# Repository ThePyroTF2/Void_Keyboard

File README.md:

Void Keyboard
====
A while ago I saw [this video](https://www.youtube.com/watch?v=H_Ym9528awM) looking at [Riskable](https://github.com/Riskable)'s [Void Switches](https://github.com/Riskable/void_switch) and it immediately caught my fancy.
They were new, cool, and most importantly, you could make em yourself with relative ease.

Now, I'm making an entire keyboard from scratch.

huh.

PCB
----
Because of the nature of the switches, a keyboard using them would be analog using hall effect sensors. Thing is, there isn't any analog hall effect PCBs on the market right now, mainly because analog keyboards as a whole are fairly new, so anybody wanting to make a keyboard using Void Switches has to make their own PCB from scratch.
And, with help from Riskable, I'm doing that.

I've never worked with PCB stuff before, but I'm learning pretty quickly and while I feel a bit out of my league progress is going rather smoothly. The PCB takes a lot of time not because it's complex, but because it's got **112** keys.

I'm lucky enough to be going to an engineering magnet program at my high school so I _should_ have access to soldering tools and the like, although I'm not 100% certain. If not, I'll find a way.

Switches
----
Don't exist right now! I do know, however, that I can use my school's 3d printers to make em.

Case
----
No clue how the case is gonna go. Could I machine it at school? should I just be happy with printing it out? does i even frickin matter? Who knows?! All I presently care about is getting the circuitry done.

Firmware
----
The most important part to making a keyboard is the firmware. Without it, keyboard no make letters on screen. Thing is, Riskable is still working on it! I hope to help him out and I'll update with more information as time goes on, but as it stands I've got nothing here.

Overall stuffs
====
This is really cool for me. I can't wait to get it done. It's hella fun to learn this stuff and make something really tangible and working and I would really recommend you do it too.

Novel things I wanna try to do with this
----
* Variable volume changes

You may notice that I have volume controls using hall effect sensors as well. In all honesty, it mainly just makes it easier to work with, but I want to try something cool with increasing and decreasing the volume.
I want to make it so that the amount that the volume increases or decreases depends on how far you push the volume button down. The 100% down amount can change using the config, but I think it'd be cool

* Turbo mode

I'm thinking I make a fun button (the most obvious key that could be replaced for fun would be the options key) toggle a kind of turbo mode, where the further down you push a key the faster it goes. I'm not sure just how useful that would be, but it's an idea.

I'm going to keep brainstorming what kind of things could be done with analog inputs.

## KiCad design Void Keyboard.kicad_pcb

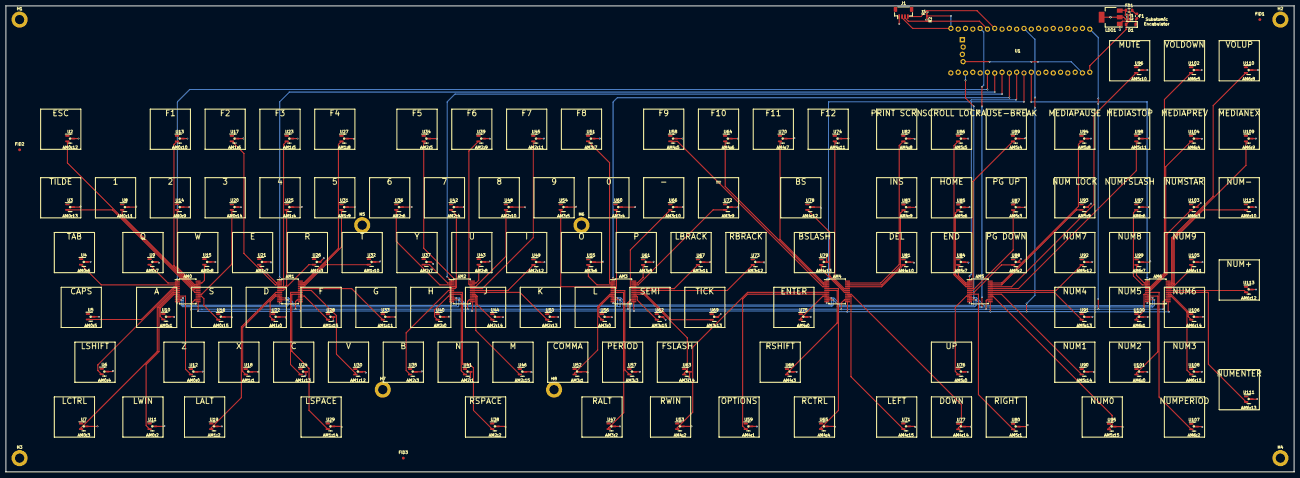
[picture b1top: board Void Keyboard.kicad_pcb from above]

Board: 2 copper layers, 447.7 x 161.9 mm, 252 parts (0 on the bottom side), 130 nets.

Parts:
AM0, AM1, AM2, AM3, AM4, AM5, AM6: CD74HC4067SM; SSOP-24_5.3x8.2mm_P0.65mm
AM0:0: Z; VoidSwitch_1u_SMD
AM0:1: VoidSwitch1U; VoidSwitch_1u_SMD
AM0:2: LWIN; VoidSwitch_1u_SMD
AM0:3: LCTRL; VoidSwitch_1.5u_SMD
AM0:4: LSHIFT; VoidSwitch_2.25u_SMD
AM0:5: CAPS; VoidSwitch_1.75u_SMD
AM0:6: TAB; VoidSwitch_1.5u_SMD
AM0:7: Q; VoidSwitch_1u_SMD
AM0:8: W; VoidSwitch_1u_SMD
AM0:9: 2; VoidSwitch_1u_SMD
AM0:10: F1; VoidSwitch_1u_SMD
AM0:11: 1; VoidSwitch_1u_SMD
AM0:12: ESC; VoidSwitch_1u_SMD
AM0:13: TILDE; VoidSwitch_1u_SMD
AM0:14: 3; VoidSwitch_1u_SMD
AM0:15: S; VoidSwitch_1u_SMD
AM1:0: D; VoidSwitch_1u_SMD
AM1:1: X; VoidSwitch_1u_SMD
AM1:2: LALT; VoidSwitch_1.25u_SMD
AM1:3: R; VoidSwitch_1u_SMD
AM1:4: 4; VoidSwitch_1u_SMD
AM1:5: F3; VoidSwitch_1u_SMD
AM1:6: F2; VoidSwitch_1u_SMD
AM1:7: E; VoidSwitch_1u_SMD
AM1:8: F4; VoidSwitch_1u_SMD
AM1:9: 5; VoidSwitch_1u_SMD
AM1:10: T; VoidSwitch_1u_SMD
AM1:11: G; VoidSwitch_1u_SMD
AM1:12: V; VoidSwitch_1u_SMD
AM1:13: C; VoidSwitch_1u_SMD
AM1:14: LSPACE; VoidSwitch_3u_SMD
AM1:15: F; VoidSwitch_1u_SMD
AM2:0: H; VoidSwitch_1u_SMD
AM2:1: N; VoidSwitch_1u_SMD
AM2:2: RSPACE; VoidSwitch_3u_SMD
AM2:3: B; VoidSwitch_1u_SMD
AM2:4: 7; VoidSwitch_1u_SMD
AM2:5: F5; VoidSwitch_1u_SMD
AM2:6: 6; VoidSwitch_1u_SMD
AM2:7: Y; VoidSwitch_1u_SMD
AM2:8: U; VoidSwitch_1u_SMD
AM2:9: F6; VoidSwitch_1u_SMD
AM2:10: 8; VoidSwitch_1u_SMD
AM2:11: F7; VoidSwitch_1u_SMD
AM2:12: I; VoidSwitch_1u_SMD
AM2:13: K; VoidSwitch_1u_SMD
AM2:14: J; VoidSwitch_1u_SMD
AM2:15: M; VoidSwitch_1u_SMD
AM3:0: L; VoidSwitch_1u_SMD
AM3:1: COMMA; VoidSwitch_1u_SMD
AM3:2: RALT; VoidSwitch_1.25u_SMD
AM3:3: PERIOD; VoidSwitch_1u_SMD
AM3:4: 0; VoidSwitch_1u_SMD
AM3:5: 9; VoidSwitch_1u_SMD
AM3:6: O; VoidSwitch_1u_SMD
AM3:7: F8; VoidSwitch_1u_SMD
AM3:8: P; VoidSwitch_1u_SMD
AM3:9: =; VoidSwitch_1u_SMD
AM3:10: -; VoidSwitch_1u_SMD
AM3:11: LBRACK; VoidSwitch_1u_SMD
AM3:12: RBRACK; VoidSwitch_1u_SMD
AM3:13: TICK; VoidSwitch_1u_SMD
AM3:14: FSLASH; VoidSwitch_1u_SMD
AM3:15: SEMI; VoidSwitch_1u_SMD
AM4:0: ENTER; VoidSwitch_2.25u_SMD
AM4:1: OPTIONS; VoidSwitch_1.25u_SMD
AM4:2: RWIN; VoidSwitch_1.25u_SMD
AM4:3: RSHIFT; VoidSwitch_2.75u_SMD
AM4:4: RCTRL; VoidSwitch_1.5u_SMD
AM4:5: F9; VoidSwitch_1u_SMD
AM4:6: F10; VoidSwitch_1u_SMD
AM4:7: F11; VoidSwitch_1u_SMD
AM4:8: PRINT SCRN; VoidSwitch_1u_SMD
AM4:9: INS; VoidSwitch_1u_SMD
AM4:10: DEL; VoidSwitch_1u_SMD
AM4:11: F12; VoidSwitch_1u_SMD
AM4:12: BS; VoidSwitch_2u_SMD
AM4:13: BSLASH; VoidSwitch_1.5u_SMD
AM4:14: DOWN; VoidSwitch_1u_SMD
AM4:15: LEFT; VoidSwitch_1u_SMD
AM5:0: UP; VoidSwitch_1u_SMD
AM5:1: RIGHT; VoidSwitch_1u_SMD
AM5:2: PG DOWN; VoidSwitch_1u_SMD
AM5:3: PG UP; VoidSwitch_1u_SMD
AM5:4: PAUSE-BREAK; VoidSwitch_1u_SMD
AM5:5: SCROLL LOCK; VoidSwitch_1u_SMD
AM5:6: HOME; VoidSwitch_1u_SMD
AM5:7: END; VoidSwitch_1u_SMD
AM5:8: MEDIAPAUSE; VoidSwitch_1u_SMD
AM5:9: NUM LOCK; VoidSwitch_1u_SMD
AM5:10: MUTE; VoidSwitch_1u_SMD
AM5:11: MEDIASTOP; VoidSwitch_1u_SMD
AM5:12: NUM7; VoidSwitch_1u_SMD
AM5:13: NUM4; VoidSwitch_1u_SMD
AM5:14: NUM1; VoidSwitch_1u_SMD
AM5:15: NUM0; VoidSwitch_2u_SMD
AM6:0: NUM2; VoidSwitch_1u_SMD
AM6:1: NUM5; VoidSwitch_1u_SMD
AM6:2: NUMPERIOD; VoidSwitch_1u_SMD
AM6:3: NUMSTAR; VoidSwitch_1u_SMD
AM6:4: MEDIAPREV; VoidSwitch_1u_SMD
AM6:5: VOLDOWN; VoidSwitch_1u_SMD
AM6:6: NUMFSLASH; VoidSwitch_1u_SMD
AM6:7: NUM8; VoidSwitch_1u_SMD
AM6:8: VOLUP; VoidSwitch_1u_SMD
AM6:9: MEDIANEX; VoidSwitch_1u_SMD
AM6:10: NUM-; VoidSwitch_1u_SMD
AM6:11: NUM9; VoidSwitch_1u_SMD
AM6:12: NUM+; VoidSwitch_2uv_SMD
AM6:13: NUMENTER; VoidSwitch_2uv_SMD
AM6:14: NUM6; VoidSwitch_1u_SMD
AM6:15: NUM3; VoidSwitch_1u_SMD
C1, C2: 10u; C_0402_1005Metric
D1: B5819W; D_SOD-123
F1: 500mA; Fuse_0603_1608Metric
FB1: 100 @ 100 MHz; L_0805_2012Metric
FID1, FID2, FID3: Fiducial; Fiducial_1mm_Mask2mm
H1, H2, H3, H4, H5, H6, H7, H8: MountingHole; MountingHole_3.2mm_M3_DIN965_Pad
J1: QWIIC; JST_SH_BM04B-SRSS-TB_1x04-1MP_P1.00mm_Vertical
LDO1: AMS1117-3.3; SOT-223-3_TabPin2
R1, R2: 2k2; R_0402_1005Metric
U1: BlackPill_STLINK
U2, U3, U4, U5, U6, U7, U8, U9, U10, U11, U12, U13, U14, U15, U16, U17, U18, U19, U20, U21, U22, U23, U24, U25, U26, U27, U28, U29, U30, U31, U32, U33, U34, U35, U36, U37, U38, U39, U40, U41, U42, U43, U44, U45, U46, U47, U48, U49, U50, U51, U52, U53, U54, U55, U56, U57, U58, U59, U60, U61, U62, U63, U64, U65, U66, U67, U68, U69, U70, U71, U72, U73, U74, U75, U76, U77, U78, U79, U80, U81, U82, U83, U84, U85, U86, U87, U88, U89, U90, U91, U92, U93, U94, U95, U96, U97, U98, U99, U100, U101, U102, U103, U104, U105, U106, U107, U108, U109, U110, U111, U112, U113: GH39FKSW; SOT-23

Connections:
+3.3VA: AM0.24 (VCC), AM1.24 (VCC), AM2.24 (VCC), AM3.24 (VCC), AM4.24 (VCC), AM5.24 (VCC), AM6.24 (VCC)
+3.3V_QWIIC: J1.2, R1.1, R2.1, U1.20 (3V3)
+3V3: C2.1, LDO1.2 (VO), U2.1 (VDD), U3.1 (VDD), U4.1 (VDD), U5.1 (VDD), U6.1 (VDD), U7.1 (VDD), U8.1 (VDD), U9.1 (VDD), U10.1 (VDD), U11.1 (VDD), U12.1 (VDD), U13.1 (VDD), U14.1 (VDD), U15.1 (VDD), U16.1 (VDD), U17.1 (VDD), U18.1 (VDD), U19.1 (VDD), U20.1 (VDD), U21.1 (VDD), U22.1 (VDD), U23.1 (VDD), U24.1 (VDD), U25.1 (VDD), U26.1 (VDD), U27.1 (VDD), U28.1 (VDD), U29.1 (VDD), U30.1 (VDD), U31.1 (VDD), U32.1 (VDD), U33.1 (VDD), U34.1 (VDD), U35.1 (VDD), U36.1 (VDD), U37.1 (VDD), U38.1 (VDD), U39.1 (VDD), U40.1 (VDD), U41.1 (VDD), U42.1 (VDD), U43.1 (VDD), U44.1 (VDD), U45.1 (VDD), U46.1 (VDD), U47.1 (VDD), U48.1 (VDD), U49.1 (VDD), U50.1 (VDD), U51.1 (VDD), U52.1 (VDD), U53.1 (VDD), U54.1 (VDD), U55.1 (VDD), U56.1 (VDD), U57.1 (VDD), U58.1 (VDD), U59.1 (VDD), U60.1 (VDD), U61.1 (VDD), U62.1 (VDD), U63.1 (VDD), U64.1 (VDD), U65.1 (VDD), U66.1 (VDD), U67.1 (VDD), U68.1 (VDD), U69.1 (VDD), U70.1 (VDD), U71.1 (VDD), U72.1 (VDD), U73.1 (VDD), U74.1 (VDD), U75.1 (VDD), U76.1 (VDD), U77.1 (VDD), U78.1 (VDD), U79.1 (VDD), U80.1 (VDD), U81.1 (VDD), U82.1 (VDD), U83.1 (VDD), U84.1 (VDD), U85.1 (VDD), U86.1 (VDD), U87.1 (VDD), U88.1 (VDD), U89.1 (VDD), U90.1 (VDD), U91.1 (VDD), U92.1 (VDD), U93.1 (VDD), U94.1 (VDD), U95.1 (VDD), U96.1 (VDD), U97.1 (VDD), U98.1 (VDD), U99.1 (VDD), U100.1 (VDD), U101.1 (VDD), U102.1 (VDD), U103.1 (VDD), U104.1 (VDD), U105.1 (VDD), U106.1 (VDD), U107.1 (VDD), U108.1 (VDD), U109.1 (VDD), U110.1 (VDD), U111.1 (VDD), U112.1 (VDD), U113.1 (VDD)
+5V: D1.2 (A), U1.40 (5V)
AM0: AM0.1 (COM), U1.26 (PA0)
AM0:0: AM0.9 (I0), U12.2 (OUT)
AM0:1: AM0.8 (I1), U10.2 (OUT)
AM0:2: AM0.7 (I2), U11.2 (OUT)
AM0:3: AM0.6 (I3), U7.2 (OUT)
AM0:4: AM0.5 (I4), U6.2 (OUT)
AM0:5: AM0.4 (I5), U5.2 (OUT)
AM0:6: AM0.3 (I6), U4.2 (OUT)
AM0:7: AM0.2 (I7), U9.2 (OUT)
AM0:8: AM0.23 (I8), U15.2 (OUT)
AM0:9: AM0.22 (I9), U14.2 (OUT)
AM0:10: AM0.21 (I10), U13.2 (OUT)
AM0:11: AM0.20 (I11), U8.2 (OUT)
AM0:12: AM0.19 (I12), U2.2 (OUT)
AM0:13: AM0.18 (I13), U3.2 (OUT)
AM0:14: AM0.17 (I14), U20.2 (OUT)
AM0:15: AM0.16 (I15), U16.2 (OUT)
AM1: AM1.1 (COM), U1.27 (PA1)
AM1:0: AM1.9 (I0), U22.2 (OUT)
AM1:1: AM1.8 (I1), U18.2 (OUT)
AM1:2: AM1.7 (I2), U19.2 (OUT)
AM1:3: AM1.6 (I3), U26.2 (OUT)
AM1:4: AM1.5 (I4), U25.2 (OUT)
AM1:5: AM1.4 (I5), U23.2 (OUT)
AM1:6: AM1.3 (I6), U17.2 (OUT)
AM1:7: AM1.2 (I7), U21.2 (OUT)
AM1:8: AM1.23 (I8), U27.2 (OUT)
AM1:9: AM1.22 (I9), U31.2 (OUT)
AM1:10: AM1.21 (I10), U32.2 (OUT)
AM1:11: AM1.20 (I11), U33.2 (OUT)
AM1:12: AM1.19 (I12), U30.2 (OUT)
AM1:13: AM1.18 (I13), U24.2 (OUT)
AM1:14: AM1.17 (I14), U29.2 (OUT)
AM1:15: AM1.16 (I15), U28.2 (OUT)
AM2: AM2.1 (COM), U1.28 (PA2)
AM2:0: AM2.9 (I0), U40.2 (OUT)
AM2:1: AM2.8 (I1), U41.2 (OUT)
AM2:2: AM2.7 (I2), U38.2 (OUT)
AM2:3: AM2.6 (I3), U35.2 (OUT)
AM2:4: AM2.5 (I4), U42.2 (OUT)
AM2:5: AM2.4 (I5), U34.2 (OUT)
AM2:6: AM2.3 (I6), U36.2 (OUT)
AM2:7: AM2.2 (I7), U37.2 (OUT)
AM2:8: AM2.23 (I8), U43.2 (OUT)
AM2:9: AM2.22 (I9), U39.2 (OUT)
AM2:10: AM2.21 (I10), U48.2 (OUT)
AM2:11: AM2.20 (I11), U45.2 (OUT)
AM2:12: AM2.19 (I12), U49.2 (OUT)
AM2:13: AM2.18 (I13), U50.2 (OUT)
AM2:14: AM2.17 (I14), U44.2 (OUT)
AM2:15: AM2.16 (I15), U46.2 (OUT)
AM3: AM3.1 (COM), U1.29 (PA3)
AM3:0: AM3.9 (I0), U56.2 (OUT)
AM3:1: AM3.8 (I1), U52.2 (OUT)
AM3:2: AM3.7 (I2), U47.2 (OUT)
AM3:3: AM3.6 (I3), U57.2 (OUT)
AM3:4: AM3.5 (I4), U60.2 (OUT)
AM3:5: AM3.4 (I5), U54.2 (OUT)
AM3:6: AM3.3 (I6), U55.2 (OUT)
AM3:7: AM3.2 (I7), U51.2 (OUT)
AM3:8: AM3.23 (I8), U61.2 (OUT)
AM3:9: AM3.22 (I9), U72.2 (OUT)
AM3:10: AM3.21 (I10), U66.2 (OUT)
AM3:11: AM3.20 (I11), U67.2 (OUT)
AM3:12: AM3.19 (I12), U73.2 (OUT)
AM3:13: AM3.18 (I13), U69.2 (OUT)
AM3:14: AM3.17 (I14), U63.2 (OUT)
AM3:15: AM3.16 (I15), U62.2 (OUT)
AM4: AM4.1 (COM), U1.30 (PA4)
AM4:0: AM4.9 (I0), U75.2 (OUT)
AM4:1: AM4.8 (I1), U59.2 (OUT)
AM4:2: AM4.7 (I2), U53.2 (OUT)
AM4:3: AM4.6 (I3), U68.2 (OUT)
AM4:4: AM4.5 (I4), U65.2 (OUT)
AM4:5: AM4.4 (I5), U58.2 (OUT)
AM4:6: AM4.3 (I6), U64.2 (OUT)
AM4:7: AM4.2 (I7), U70.2 (OUT)
AM4:8: AM4.23 (I8), U82.2 (OUT)
AM4:9: AM4.22 (I9), U83.2 (OUT)
AM4:10: AM4.21 (I10), U81.2 (OUT)
AM4:11: AM4.20 (I11), U74.2 (OUT)
AM4:12: AM4.19 (I12), U78.2 (OUT)
AM4:13: AM4.18 (I13), U79.2 (OUT)
AM4:14: AM4.17 (I14), U77.2 (OUT)
AM4:15: AM4.16 (I15), U71.2 (OUT)
AM5: AM5.1 (COM), U1.31 (PA5)
AM5:0: AM5.9 (I0), U76.2 (OUT)
AM5:1: AM5.8 (I1), U80.2 (OUT)
AM5:2: AM5.7 (I2), U88.2 (OUT)
AM5:3: AM5.6 (I3), U87.2 (OUT)
AM5:4: AM5.5 (I4), U89.2 (OUT)
AM5:5: AM5.4 (I5), U86.2 (OUT)
AM5:6: AM5.3 (I6), U85.2 (OUT)
AM5:7: AM5.2 (I7), U84.2 (OUT)
AM5:8: AM5.23 (I8), U94.2 (OUT)
AM5:9: AM5.22 (I9), U93.2 (OUT)
AM5:10: AM5.21 (I10), U96.2 (OUT)
AM5:11: AM5.20 (I11), U98.2 (OUT)
AM5:12: AM5.19 (I12), U92.2 (OUT)
AM5:13: AM5.18 (I13), U91.2 (OUT)
AM5:14: AM5.17 (I14), U90.2 (OUT)
AM5:15: AM5.16 (I15), U95.2 (OUT)
AM6: AM6.1 (COM), U1.32 (PA6)
AM6:0: AM6.9 (I0), U101.2 (OUT)
AM6:1: AM6.8 (I1), U100.2 (OUT)
AM6:2: AM6.7 (I2), U107.2 (OUT)
AM6:3: AM6.6 (I3), U103.2 (OUT)
AM6:4: AM6.5 (I4), U104.2 (OUT)
AM6:5: AM6.4 (I5), U102.2 (OUT)
AM6:6: AM6.3 (I6), U97.2 (OUT)
AM6:7: AM6.2 (I7), U99.2 (OUT)
AM6:8: AM6.23 (I8), U110.2 (OUT)
AM6:9: AM6.22 (I9), U109.2 (OUT)
AM6:10: AM6.21 (I10), U112.2 (OUT)
AM6:11: AM6.20 (I11), U105.2 (OUT)
AM6:12: AM6.19 (I12), U113.2 (OUT)
AM6:13: AM6.18 (I13), U111.2 (OUT)
AM6:14: AM6.17 (I14), U106.2 (OUT)
AM6:15: AM6.16 (I15), U108.2 (OUT)
GND: AM0.12 (GND), AM0.15 (~E), AM1.12 (GND), AM1.15 (~E), AM2.12 (GND), AM2.15 (~E), AM3.12 (GND), AM3.15 (~E), AM4.12 (GND), AM4.15 (~E), AM5.12 (GND), AM5.15 (~E), AM6.12 (GND), AM6.15 (~E), C1.2, C2.2, J1.1, LDO1.1 (GND), U1.19 (GND), U1.39 (GND), U1.44 (GND), U2.3 (GND), U3.3 (GND), U4.3 (GND), U5.3 (GND), U6.3 (GND), U7.3 (GND), U8.3 (GND), U9.3 (GND), U10.3 (GND), U11.3 (GND), U12.3 (GND), U13.3 (GND), U14.3 (GND), U15.3 (GND), U16.3 (GND), U17.3 (GND), U18.3 (GND), U19.3 (GND), U20.3 (GND), U21.3 (GND), U22.3 (GND), U23.3 (GND), U24.3 (GND), U25.3 (GND), U26.3 (GND), U27.3 (GND), U28.3 (GND), U29.3 (GND), U30.3 (GND), U31.3 (GND), U32.3 (GND), U33.3 (GND), U34.3 (GND), U35.3 (GND), U36.3 (GND), U37.3 (GND), U38.3 (GND), U39.3 (GND), U40.3 (GND), U41.3 (GND), U42.3 (GND), U43.3 (GND), U44.3 (GND), U45.3 (GND), U46.3 (GND), U47.3 (GND), U48.3 (GND), U49.3 (GND), U50.3 (GND), U51.3 (GND), U52.3 (GND), U53.3 (GND), U54.3 (GND), U55.3 (GND), U56.3 (GND), U57.3 (GND), U58.3 (GND), U59.3 (GND), U60.3 (GND), U61.3 (GND), U62.3 (GND), U63.3 (GND), U64.3 (GND), U65.3 (GND), U66.3 (GND), U67.3 (GND), U68.3 (GND), U69.3 (GND), U70.3 (GND), U71.3 (GND), U72.3 (GND), U73.3 (GND), U74.3 (GND), U75.3 (GND), U76.3 (GND), U77.3 (GND), U78.3 (GND), U79.3 (GND), U80.3 (GND), U81.3 (GND), U82.3 (GND), U83.3 (GND), U84.3 (GND), U85.3 (GND), U86.3 (GND), U87.3 (GND), U88.3 (GND), U89.3 (GND), U90.3 (GND), U91.3 (GND), U92.3 (GND), U93.3 (GND), U94.3 (GND), U95.3 (GND), U96.3 (GND), U97.3 (GND), U98.3 (GND), U99.3 (GND), U100.3 (GND), U101.3 (GND), U102.3 (GND), U103.3 (GND), U104.3 (GND), U105.3 (GND), U106.3 (GND), U107.3 (GND), U108.3 (GND), U109.3 (GND), U110.3 (GND), U111.3 (GND), U112.3 (GND), U113.3 (GND)
PB6_SCL1: J1.4, R1.2, U1.14 (PB6)
PB7_SDA1: J1.3, R2.2, U1.15 (PB7)
SELECT0: AM0.10 (S0), AM1.10 (S0), AM2.10 (S0), AM3.10 (S0), AM4.10 (S0), AM5.10 (S0), AM6.10 (S0), U1.23 (PC14)
SELECT1: AM0.11 (S1), AM1.11 (S1), AM2.11 (S1), AM3.11 (S1), AM4.11 (S1), AM5.11 (S1), AM6.11 (S1), U1.16 (PB8)
SELECT2: AM0.14 (S2), AM1.14 (S2), AM2.14 (S2), AM3.14 (S2), AM4.14 (S2), AM5.14 (S2), AM6.14 (S2), U1.1 (PB12)
SELECT3: AM0.13 (S3), AM1.13 (S3), AM2.13 (S3), AM3.13 (S3), AM4.13 (S3), AM5.13 (S3), AM6.13 (S3), U1.10 (PA15)

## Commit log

2022-04-20 Add PCB
2022-04-20 Delete Big Boi Keyboard.kicad_pcb
    couldn't frickin rename it.
2022-04-20 Add Void Keyboard
